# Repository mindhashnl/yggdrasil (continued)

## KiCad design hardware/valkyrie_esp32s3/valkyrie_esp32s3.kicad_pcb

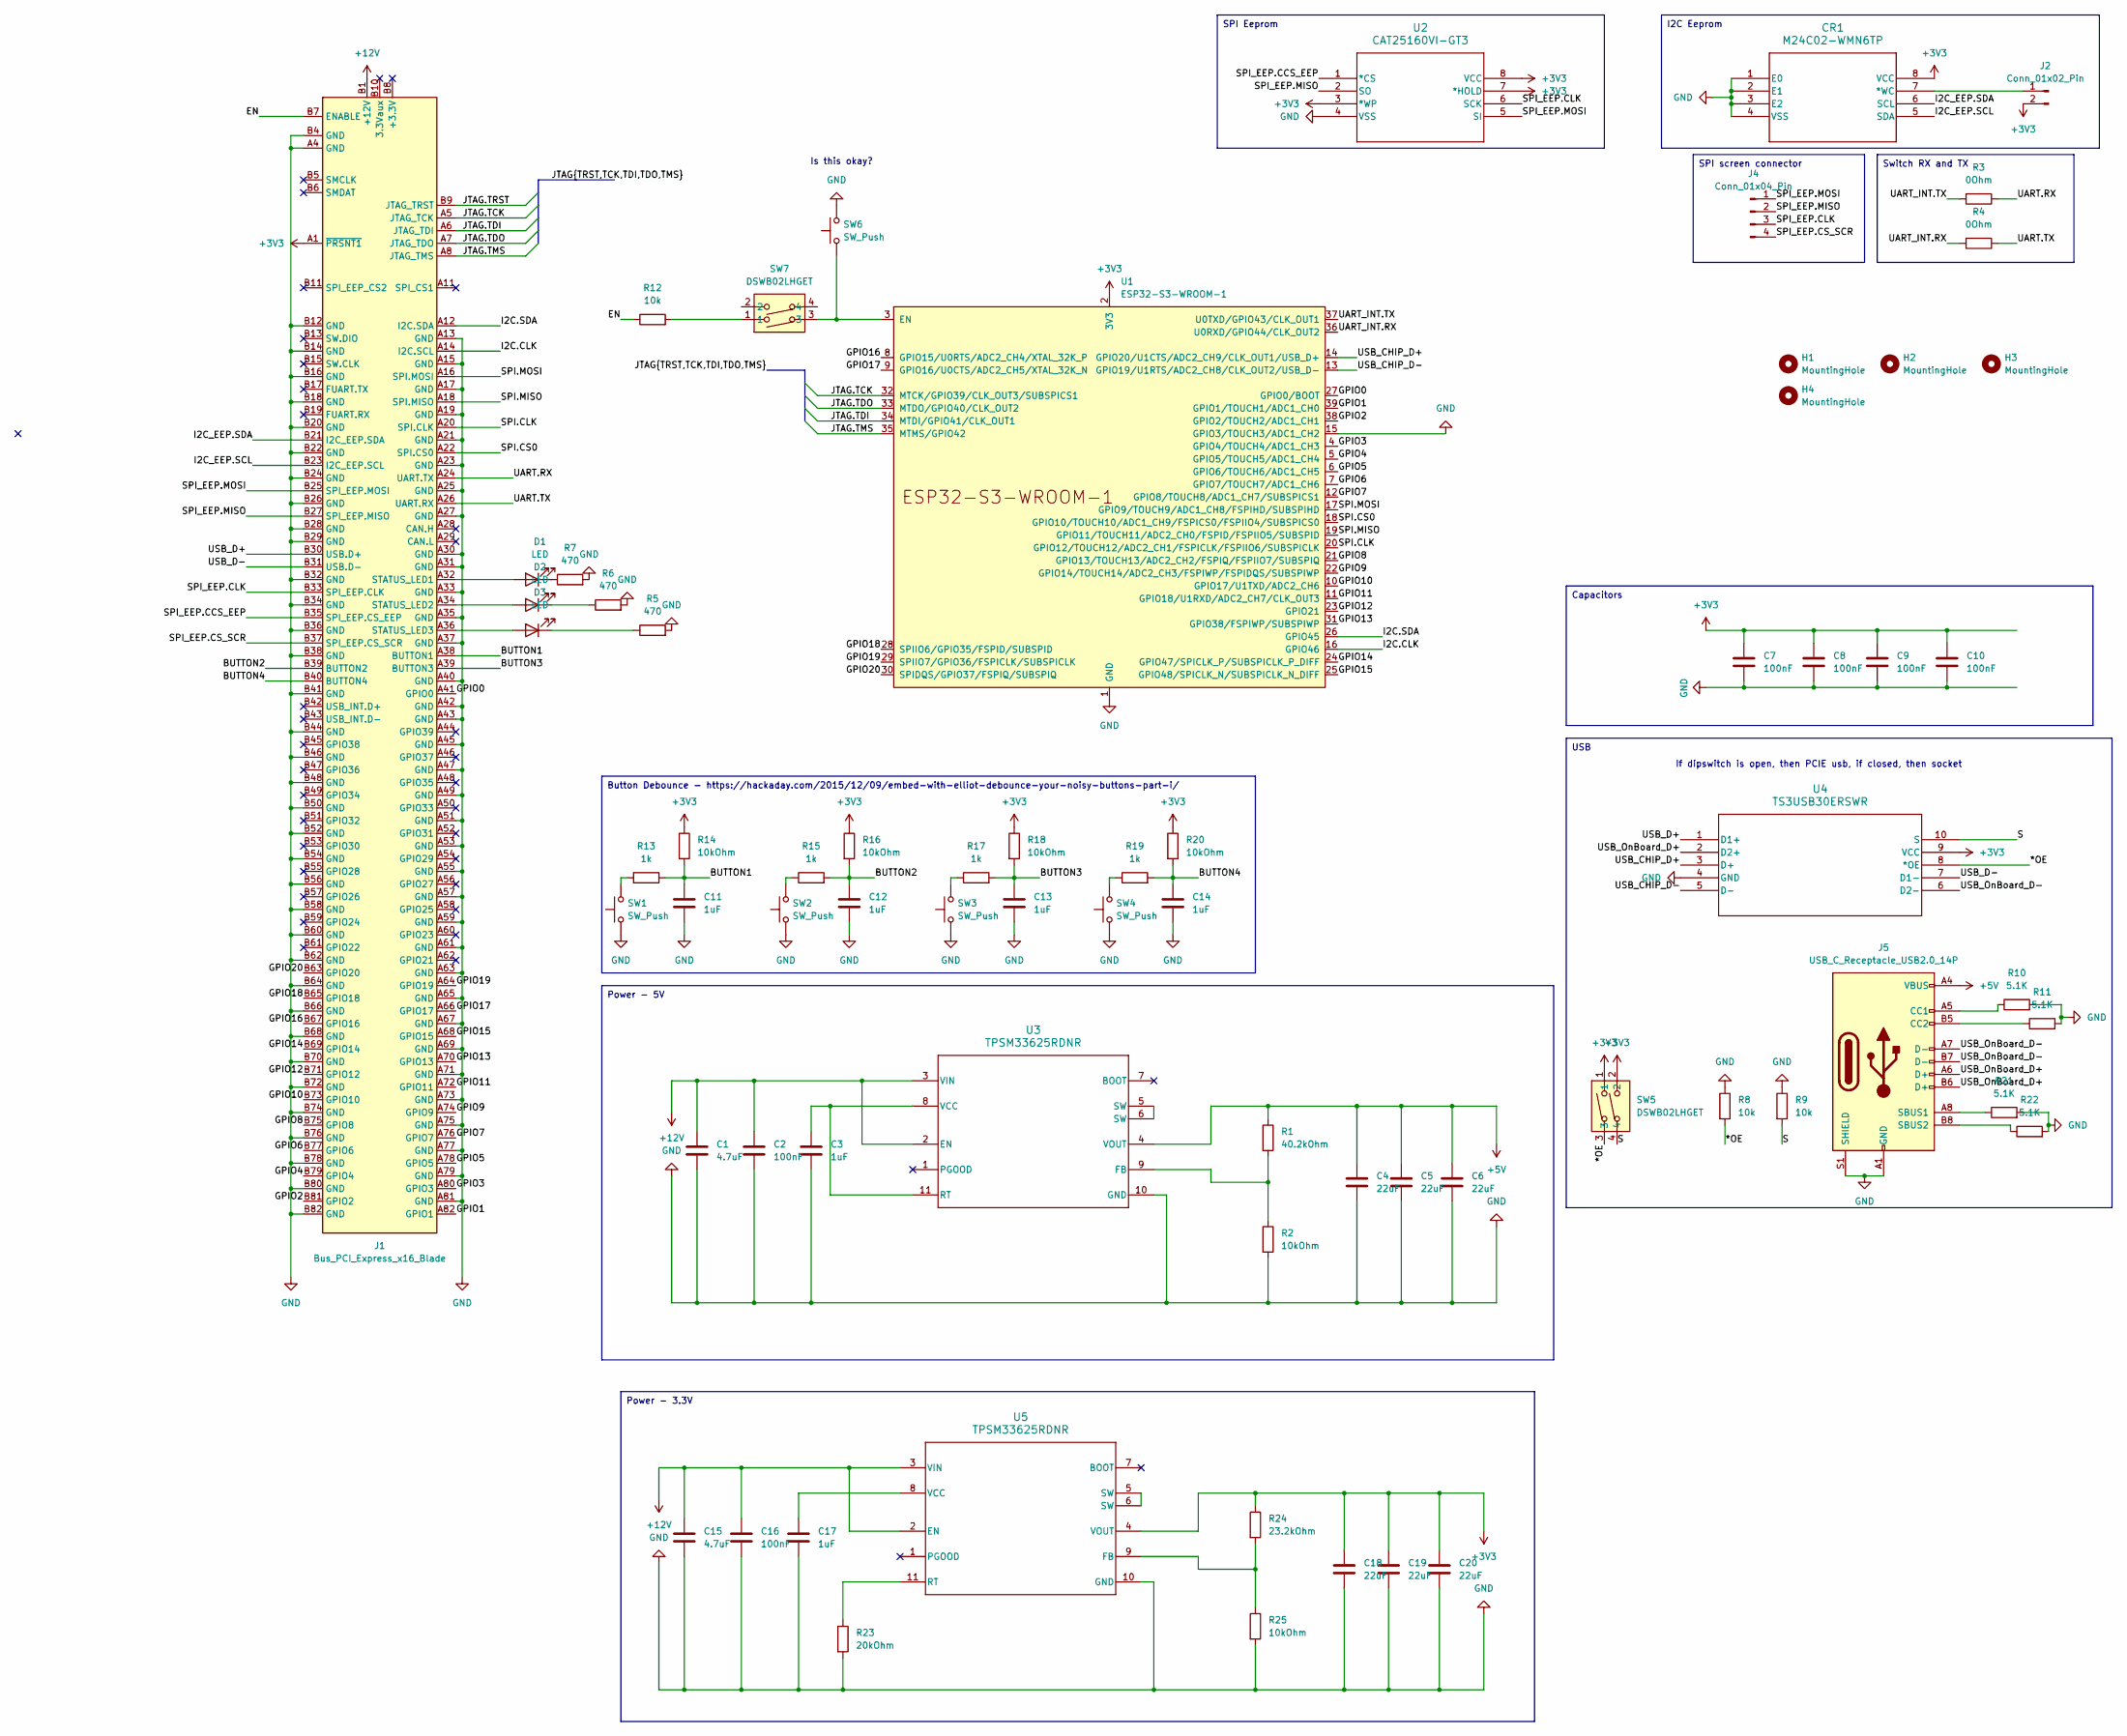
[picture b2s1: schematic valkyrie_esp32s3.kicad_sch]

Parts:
C1, C15: 4.7uF; C_0805_2012Metric
C2, C7, C8, C9, C10, C16: 100nF; C_0805_2012Metric
C3, C11, C12, C13, C14, C17: 1uF; C_0805_2012Metric
C4, C5, C6, C18, C19, C20: 22uF; C_0805_2012Metric
CR1: M24C02-WMN6TP; SO-8_STM
D1, D2, D3: LED; LED_0805_2012Metric
H1, H2, H3, H4: MountingHole; MountingHole_3.2mm_M3_Pad_TopBottom
J1: Bus_PCI_Express_x16_Blade; BUS_PCIexpress_x16
J2: Conn_01x02_Pin; PinHeader_1x02_P2.54mm_Vertical
J4: Conn_01x04_Pin; PinHeader_1x04_P2.54mm_Vertical
J5: USB_C_Receptacle_USB2.0_14P; USB_C_Receptacle_G-Switch_GT-USB-7010ASV
R1: 40.2kOhm; R_0805_2012Metric
R2, R14, R16, R18, R20, R25: 10kOhm; R_0805_2012Metric
R3, R4: 0Ohm; R_0805_2012Metric
R5, R6, R7: 470; R_0805_2012Metric
R8, R9, R12: 10k; R_0805_2012Metric
R10, R11, R21, R22: 5.1K; R_0805_2012Metric
R13, R15, R17, R19: 1k; R_0805_2012Metric
R23: 20kOhm; R_0805_2012Metric
R24: 23.2kOhm; R_0805_2012Metric
SW1, SW2, SW3, SW4, SW6: SW_Push; SW_Push_1P1T_XKB_TS-1187A
SW5, SW7: DSWB02LHGET; SW-TH_DSWB02LHGET; LCSC Part C99421
U1: ESP32-S3-WROOM-1
U2: CAT25160VI-GT3; SOIC8_ONS
U3, U5: TPSM33625RDNR; RDN0011A-MFG_custom
U4: TS3USB30ERSWR; RSW10_TEX

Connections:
+3V3: C7.1, C8.1, C9.1, C10.1, C18.1, C19.1, C20.1, CR1.8 (VCC), J1.A1 (~PRSNT1), J2.2, R14.1, R16.1, R18.1, R20.1, R24.1, SW5.1, SW5.2, U1.2 (3V3), U2.3 (*WP), U2.7 (*HOLD), U2.8 (VCC), U4.9 (VCC), U5.4 (VOUT)
+5V: C4.1, C5.1, C6.1, J5.A4 (VBUS), J5.A9 (VBUS), J5.B4 (VBUS), J5.B9 (VBUS), R1.1, U3.4 (VOUT)
+12V: C1.1, C2.1, C15.1, C16.1, J1.A2 (+12V), J1.A3 (+12V), J1.B1 (+12V), J1.B2 (+12V), J1.B3 (+12V), U3.2 (EN), U3.3 (VIN), U5.2 (EN), U5.3 (VIN)
/*OE: R8.2, SW5.3, U4.8 (*OE)
/BUTTON1: C11.1, J1.A38 (BUTTON1), R13.2, R14.2
/BUTTON2: C12.1, J1.B39 (BUTTON2), R15.2, R16.2
/BUTTON3: C13.1, J1.A39 (BUTTON3), R17.2, R18.2
/BUTTON4: C14.1, J1.B40 (BUTTON4), R19.2, R20.2
/EN: J1.B7 (ENABLE), R12.1
/GPIO0: J1.A41 (GPIO0), U1.27 (GPIO0/BOOT)
/GPIO1: J1.A82 (GPIO1), U1.39 (GPIO1/TOUCH1/ADC1_CH0)
/GPIO2: J1.B81 (GPIO2), U1.38 (GPIO2/TOUCH2/ADC1_CH1)
/GPIO3: J1.A80 (GPIO3), U1.4 (GPIO4/TOUCH4/ADC1_CH3)
/GPIO4: J1.B79 (GPIO4), U1.5 (GPIO5/TOUCH5/ADC1_CH4)
/GPIO5: J1.A78 (GPIO5), U1.6 (GPIO6/TOUCH6/ADC1_CH5)
/GPIO6: J1.B77 (GPIO6), U1.7 (GPIO7/TOUCH7/ADC1_CH6)
/GPIO7: J1.A76 (GPIO7), U1.12 (GPIO8/TOUCH8/ADC1_CH7/SUBSPICS1)
/GPIO8: J1.B75 (GPIO8), U1.21 (GPIO13/TOUCH13/ADC2_CH2/FSPIQ/FSPIIO7/S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)
/GPIO9: J1.A74 (GPIO9), U1.22 (GPIO14/TOUCH14/ADC2_CH3/FSPIWP/FSPIDQS/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)
/GPIO10: J1.B73 (GPIO10), U1.10 (GPIO17/U1TXD/ADC2_CH6)
/GPIO11: J1.A72 (GPIO11), U1.11 (GPIO18/U1RXD/ADC2_CH7/CLK_OUT3)
/GPIO12: J1.B71 (GPIO12), U1.23 (GPIO21)
/GPIO13: J1.A70 (GPIO13), U1.31 (GPIO38/FSPIWP/SUBSPIWP)
/GPIO14: J1.B69 (GPIO14), U1.24 (GPIO47/SPICLK_P/SUBSPICLK_P_DIFF)
/GPIO15: J1.A68 (GPIO15), U1.25 (GPIO48/SPICLK_N/SUBSPICLK_N_DIFF)
/GPIO16: J1.B67 (GPIO16), U1.8 (GPIO15/U0RTS/ADC2_CH4/XTAL_32K_P)
/GPIO17: J1.A66 (GPIO17), U1.9 (GPIO16/U0CTS/ADC2_CH5/XTAL_32K_N)
/GPIO18: J1.B65 (GPIO18), U1.28 (SPIIO6/GPIO35/FSPID/SUBSPID)
/GPIO19: J1.A64 (GPIO19), U1.29 (SPIIO7/GPIO36/FSPICLK/SUBSPICLK)
/GPIO20: J1.B63 (GPIO20), U1.30 (SPIDQS/GPIO37/FSPIQ/SUBSPIQ)
/I2C.CLK: J1.A14 (I2C.SCL), U1.16 (GPIO46)
/I2C.SDA: J1.A12 (I2C.SDA), U1.26 (GPIO45)
/I2C_EEP.SCL: CR1.5 (SDA), J1.B23 (I2C_EEP.SCL)
/I2C_EEP.SDA: CR1.6 (SCL), J1.B21 (I2C_EEP.SDA)
/JTAG.TCK: J1.A5 (JTAG_TCK), U1.32 (MTCK/GPIO39/CLK_OUT3/SUBSPICS1)
/JTAG.TDI: J1.A6 (JTAG_TDI), U1.34 (MTDI/GPIO41/CLK_OUT1)
/JTAG.TDO: J1.A7 (JTAG_TDO), U1.33 (MTDO/GPIO40/CLK_OUT2)
/JTAG.TMS: J1.A8 (JTAG_TMS), U1.35 (MTMS/GPIO42)
/JTAG.TRST: J1.B9 (JTAG_TRST)
/S: R9.2, SW5.4, U4.10 (S)
/SPI.CLK: J1.A20 (SPI.CLK), U1.20 (GPIO12/TOUCH12/ADC2_CH1/FSPICLK/FSPIIO6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)
/SPI.CS0: J1.A22 (SPI.CS0), U1.18 (GPIO10/TOUCH10/ADC1_CH9/FSPICS0/FSPIIO4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)
/SPI.MISO: J1.A18 (SPI.MISO), U1.19 (GPIO11/TOUCH11/ADC2_CH0/FSPID/FSPIIO5/S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)
/SPI.MOSI: J1.A16 (SPI.MOSI), U1.17 (GPIO9/TOUCH9/ADC1_CH8/FSPIHD/SUBSPIHD)
/SPI_EEP.CCS_EEP: J1.B35 (SPI_EEP.CS_EEP), U2.1 (*CS)
/SPI_EEP.CLK: J1.B33 (SPI_EEP.CLK), J4.3, U2.6 (SCK)
/SPI_EEP.CS_SCR: J1.B37 (SPI_EEP.CS_SCR), J4.4
/SPI_EEP.MISO: J1.B27 (SPI_EEP.MISO), J4.2, U2.2 (SO)
/SPI_EEP.MOSI: J1.B25 (SPI_EEP.MOSI), J4.1, U2.5 (SI)
/UART.RX: J1.A24 (UART.TX), R3.1
/UART.TX: J1.A26 (UART.RX), R4.1
/UART_INT.RX: R4.2, U1.36 (U0RXD/GPIO44/CLK_OUT2)
/UART_INT.TX: R3.2, U1.37 (U0TXD/GPIO43/CLK_OUT1)
/USB_CHIP_D+: U1.14 (GPIO20/U1CTS/ADC2_CH9/CLK_OUT1/USB_D+), U4.3 (D+)
/USB_CHIP_D-: U1.13 (GPIO19/U1RTS/ADC2_CH8/CLK_OUT2/USB_D-), U4.5 (D-)
/USB_D+: J1.B30 (USB.D+), U4.1 (D1+)
/USB_D-: J1.B31 (USB.D-), U4.7 (D1-)
/USB_OnBoard_D+: J5.A6 (D+), J5.B6 (D+), U4.2 (D2+)
/USB_OnBoard_D-: J5.A7 (D-), J5.B7 (D-), U4.6 (D2-)
GND: C1.2, C2.2, C3.2, C4.2, C5.2, C6.2, C7.2, C8.2, C9.2, C10.2, C11.2, C12.2, C13.2, C14.2, C15.2, C16.2, C17.2, C18.2, C19.2, C20.2, CR1.1 (E0), CR1.2 (E1), CR1.3 (E2), CR1.4 (VSS), J1.A4 (GND), J1.A13 (GND), J1.A15 (GND), J1.A17 (GND), J1.A19 (GND), J1.A21 (GND), J1.A23 (GND), J1.A25 (GND), J1.A27 (GND), J1.A30 (GND), J1.A31 (GND), J1.A33 (GND), J1.A35 (GND), J1.A37 (GND), J1.A40 (GND), J1.A42 (GND), J1.A43 (GND), J1.A45 (GND), J1.A47 (GND), J1.A49 (GND), J1.A51 (GND), J1.A53 (GND), J1.A55 (GND), J1.A57 (GND), J1.A59 (GND), J1.A61 (GND), J1.A63 (GND), J1.A65 (GND), J1.A67 (GND), J1.A69 (GND), J1.A71 (GND), J1.A73 (GND), J1.A75 (GND), J1.A77 (GND), J1.A79 (GND), J1.A81 (GND), J1.B4 (GND), J1.B12 (GND), J1.B14 (GND), J1.B16 (GND), J1.B18 (GND), J1.B20 (GND), J1.B22 (GND), J1.B24 (GND), J1.B26 (GND), J1.B28 (GND), J1.B29 (GND), J1.B32 (GND), J1.B34 (GND), J1.B36 (GND), J1.B38 (GND), J1.B41 (GND), J1.B44 (GND), J1.B46 (GND), J1.B48 (GND), J1.B50 (GND), J1.B52 (GND), J1.B54 (GND), J1.B56 (GND), J1.B58 (GND), J1.B60 (GND), J1.B62 (GND), J1.B64 (GND), J1.B66 (GND), J1.B68 (GND), J1.B70 (GND), J1.B72 (GND), J1.B74 (GND), J1.B76 (GND), J1.B78 (GND), J1.B80 (GND), J1.B82 (GND), J5.A1 (GND), J5.A12 (GND), J5.B1 (GND), J5.B12 (GND), J5.S1 (SHIELD), R2.2, R5.2, R6.2, R7.2, R8.1, R9.1, R10.2, R11.2, R21.2, R22.2, R23.2, R25.2, SW1.1, SW2.1, SW3.1, SW4.1, SW6.2, U1.1 (GND), U1.15 (GPIO3/TOUCH3/ADC1_CH2), U1.40 (GND), U1.41 (GND), U2.4 (VSS), U3.10 (GND), U4.4 (GND), U5.10 (GND)
unnamed: CR1.7 (*WC), J2.1
unnamed: D1.2 (A), J1.A32 (STATUS_LED1)
unnamed: D1.1 (K), R7.1
unnamed: D2.2 (A), J1.A34 (STATUS_LED2)
unnamed: D2.1 (K), R6.1
unnamed: D3.2 (A), J1.A36 (STATUS_LED3)
unnamed: D3.1 (K), R5.1
unnamed: J5.A5 (CC1), R10.1
unnamed: J5.B5 (CC2), R11.1
unnamed: J5.A8 (SBUS1), R21.1
unnamed: J5.B8 (SBUS2), R22.1
unnamed: R12.2, SW7.1
unnamed: R13.1, SW1.2
unnamed: R15.1, SW2.2
unnamed: R17.1, SW3.2
unnamed: R19.1, SW4.2
unnamed: SW6.1, SW7.3, U1.3 (EN)
unnamed: R1.2, R2.1, U3.9 (FB)
unnamed: C3.1, U3.8 (VCC), U3.11 (RT)
unnamed: U3.5 (SW), U3.6 (SW)
unnamed: R24.2, R25.1, U5.9 (FB)
unnamed: R23.1, U5.11 (RT)
unnamed: U5.5 (SW), U5.6 (SW)
unnamed: C17.1, U5.8 (VCC)

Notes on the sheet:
Switch RX and TX
Power - 5V
USB
I2C Eeprom
SPI screen connector
SPI Eeprom
Capacitors
Button Debounce - https://hackaday.com/2015/12/09/embed-with-elliot-debounce-your-noisy-buttons-part-i/
Power - 3.3V
Is this okay?
If dipswitch is open, then PCIE usb, if closed, then socket

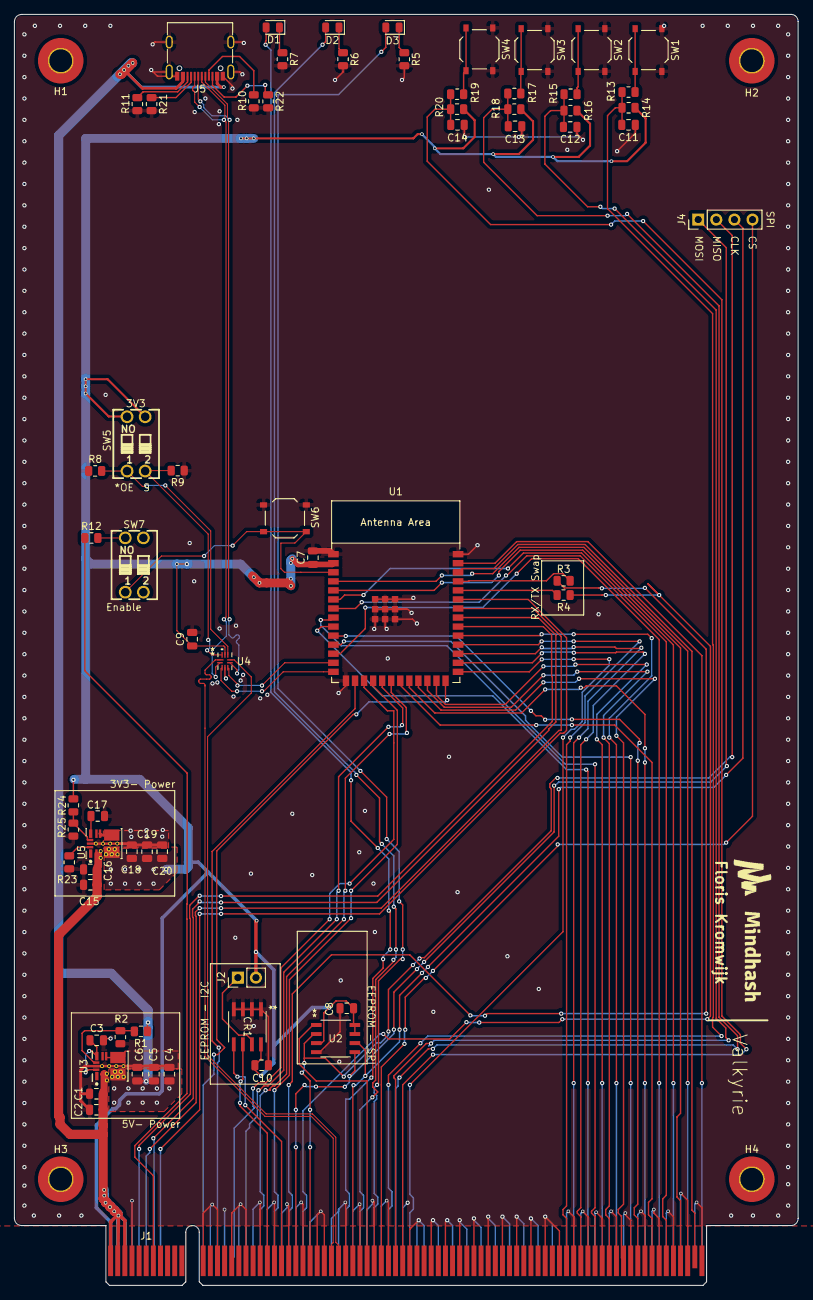
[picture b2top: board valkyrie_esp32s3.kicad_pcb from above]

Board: 4 copper layers, 110.0 x 178.4 mm, 69 parts (0 on the bottom side), 83 nets.

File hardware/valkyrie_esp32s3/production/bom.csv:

Designator,Footprint,Quantity,Value,LCSC Part #
"C1, C15",0805,2,4.7uF,
"C10, C16, C2, C7, C8, C9",0805,6,100nF,
"C11, C12, C13, C14, C17, C3",0805,6,1uF,
"C18, C19, C20, C4, C5, C6",0805,6,22uF,
CR1,SO-8_STM,1,M24C02-WMN6TP,
"D1, D2, D3",0805,3,LED,
J1,BUS_PCIexpress_x16,1,Bus_PCI_Express_x16_Blade,
J2,PinHeader_1x02_P2.54mm_Vertical,1,Conn_01x02_Pin,
J4,PinHeader_1x04_P2.54mm_Vertical,1,Conn_01x04_Pin,
J5,USB_C_Receptacle_G-Switch_GT-USB-7010ASV,1,USB_C_Receptacle_USB2.0_14P,
R1,0805,1,40.2kOhm,
"R10, R11, R21, R22",0805,4,5.1K,
"R12, R8, R9",0805,3,10k,
"R13, R15, R17, R19",0805,4,1k,
"R14, R16, R18, R2, R20, R25",0805,6,10kOhm,
R23,0805,1,20kOhm,
R24,0805,1,23.2kOhm,
"R3, R4",0805,2,0Ohm,
"R5, R6, R7",0805,3,470,
"SW1, SW2, SW3, SW4, SW6",SW_Push_1P1T_XKB_TS-1187A,5,SW_Push,
"SW5, SW7",SW-TH_DSWB02LHGET,2,DSWB02LHGET,
U1,ESP32-S3-WROOM-1,1,ESP32-S3-WROOM-1,
U2,SOIC8_ONS,1,CAT25160VI-GT3,
"U3, U5",RDN0011A-MFG_custom,2,TPSM33625RDNR,
U4,RSW10_TEX,1,TS3USB30ERSWR,

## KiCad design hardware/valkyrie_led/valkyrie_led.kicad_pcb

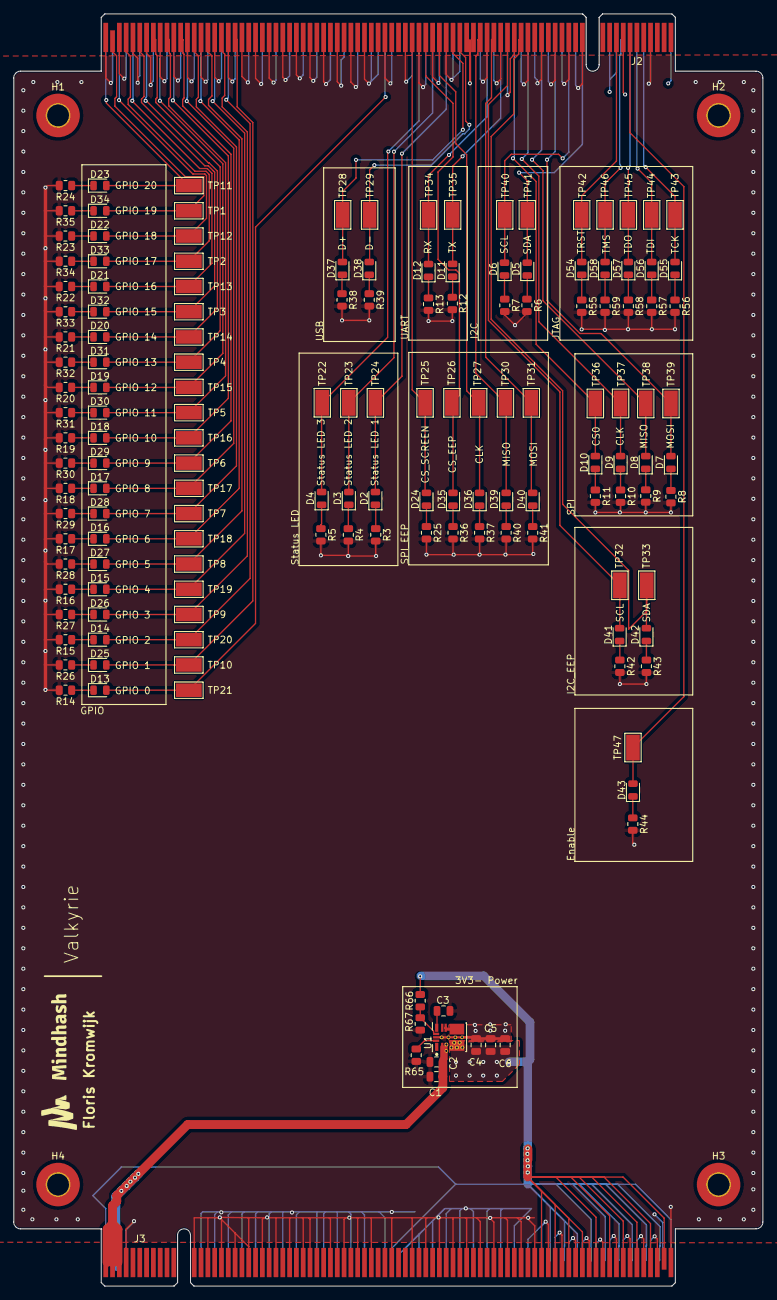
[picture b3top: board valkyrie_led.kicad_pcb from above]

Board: 4 copper layers, 110.0 x 186.8 mm, 157 parts (0 on the bottom side), 102 nets.

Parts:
C1: 4.7uF; C_0805_2012Metric
C2: 100nF; C_0805_2012Metric
C3: 1uF; C_0805_2012Metric
C4, C5, C6: 22uF; C_0805_2012Metric
D2, D3, D4, D5, D6, D7, D8, D9, D10, D11, D12, D13, D14, D15, D16, D17, D18, D19, D20, D21, D22, D23, D24, D25, D26, D27, D28, D29, D30, D31, D32, D33, D34, D35, D36, D37, D38, D39, D40, D41, D42, D43, D54, D55, D56, D57, D58: LED; LED_0805_2012Metric
H1, H2, H3, H4: MountingHole; MountingHole_3.2mm_M3_Pad_TopBottom
J2, J3: Bus_PCI_Express_x16_Blade; BUS_PCIexpress_x16
R3, R4, R5, R6, R7, R8, R9, R10, R11, R12, R13, R14, R15, R16, R17, R18, R19, R20, R21, R22, R23, R24, R25, R26, R27, R28, R29, R30, R31, R32, R33, R34, R35, R36, R37, R38, R39, R40, R41, R42, R43, R44, R55, R56, R57, R58, R59: 470; R_0805_2012Metric
R65: 20kOhm; R_0805_2012Metric
R66: 23.2kOhm; R_0805_2012Metric
R67: 10kOhm; R_0805_2012Metric
TP1, TP2, TP3, TP4, TP5, TP6, TP7, TP8, TP9, TP10, TP11, TP12, TP13, TP14, TP15, TP16, TP17, TP18, TP19, TP20, TP21, TP22, TP23, TP24, TP25, TP26, TP27, TP28, TP29, TP30, TP31, TP32, TP33, TP34, TP35, TP36, TP37, TP38, TP39, TP40, TP41, TP42, TP43, TP44, TP45, TP46, TP47: TestPoint; TestPoint_Keystone_5019_Minature
U1: TPSM33625RDNR; RDN0011A-MFG_custom

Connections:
+3.3V: J2.A1 (~PRSNT1), J2.A9 (+3.3V), J2.A10 (+3.3V), J2.B8 (+3.3V)
+3V3: C4.1, C5.1, C6.1, J3.A1 (~PRSNT1), J3.A41 (GPIO0), J3.A64 (GPIO19), J3.A66 (GPIO17), J3.A68 (GPIO15), J3.A70 (GPIO13), J3.A72 (GPIO11), J3.A74 (GPIO9), J3.A76 (GPIO7), J3.A78 (GPIO5), J3.A80 (GPIO3), J3.A82 (GPIO1), J3.B63 (GPIO20), J3.B65 (GPIO18), J3.B67 (GPIO16), J3.B69 (GPIO14), J3.B71 (GPIO12), J3.B73 (GPIO10), J3.B75 (GPIO8), J3.B77 (GPIO6), J3.B79 (GPIO4), J3.B81 (GPIO2), R66.1, U1.4 (VOUT)
+12V: C1.1, C2.1, J3.A2 (+12V), J3.A3 (+12V), J3.B1 (+12V), J3.B2 (+12V), J3.B3 (+12V), U1.2 (EN), U1.3 (VIN)
GND: C1.2, C2.2, C3.2, C4.2, C5.2, C6.2, J2.A4 (GND), J2.A13 (GND), J2.A15 (GND), J2.A17 (GND), J2.A19 (GND), J2.A21 (GND), J2.A23 (GND), J2.A25 (GND), J2.A27 (GND), J2.A30 (GND), J2.A31 (GND), J2.A33 (GND), J2.A35 (GND), J2.A37 (GND), J2.A40 (GND), J2.A42 (GND), J2.A43 (GND), J2.A45 (GND), J2.A47 (GND), J2.A49 (GND), J2.A51 (GND), J2.A53 (GND), J2.A55 (GND), J2.A57 (GND), J2.A59 (GND), J2.A61 (GND), J2.A63 (GND), J2.A65 (GND), J2.A67 (GND), J2.A69 (GND), J2.A71 (GND), J2.A73 (GND), J2.A75 (GND), J2.A77 (GND), J2.A79 (GND), J2.A81 (GND), J2.B4 (GND), J2.B12 (GND), J2.B14 (GND), J2.B16 (GND), J2.B18 (GND), J2.B20 (GND), J2.B22 (GND), J2.B24 (GND), J2.B26 (GND), J2.B28 (GND), J2.B29 (GND), J2.B32 (GND), J2.B34 (GND), J2.B36 (GND), J2.B38 (GND), J2.B41 (GND), J2.B44 (GND), J2.B46 (GND), J2.B48 (GND), J2.B50 (GND), J2.B52 (GND), J2.B54 (GND), J2.B56 (GND), J2.B58 (GND), J2.B60 (GND), J2.B62 (GND), J2.B64 (GND), J2.B66 (GND), J2.B68 (GND), J2.B70 (GND), J2.B72 (GND), J2.B74 (GND), J2.B76 (GND), J2.B78 (GND), J2.B80 (GND), J2.B82 (GND), J3.A4 (GND), J3.A13 (GND), J3.A15 (GND), J3.A17 (GND), J3.A19 (GND), J3.A21 (GND), J3.A23 (GND), J3.A25 (GND), J3.A27 (GND), J3.A30 (GND), J3.A31 (GND), J3.A33 (GND), J3.A35 (GND), J3.A37 (GND), J3.A40 (GND), J3.A42 (GND), J3.A43 (GND), J3.A45 (GND), J3.A47 (GND), J3.A49 (GND), J3.A51 (GND), J3.A53 (GND), J3.A55 (GND), J3.A57 (GND), J3.A59 (GND), J3.A61 (GND), J3.A63 (GND), J3.A65 (GND), J3.A67 (GND), J3.A69 (GND), J3.A71 (GND), J3.A73 (GND), J3.A75 (GND), J3.A77 (GND), J3.A79 (GND), J3.A81 (GND), J3.B4 (GND), J3.B12 (GND), J3.B14 (GND), J3.B16 (GND), J3.B18 (GND), J3.B20 (GND), J3.B22 (GND), J3.B24 (GND), J3.B26 (GND), J3.B28 (GND), J3.B29 (GND), J3.B32 (GND), J3.B34 (GND), J3.B36 (GND), J3.B38 (GND), J3.B41 (GND), J3.B44 (GND), J3.B46 (GND), J3.B48 (GND), J3.B50 (GND), J3.B52 (GND), J3.B54 (GND), J3.B56 (GND), J3.B58 (GND), J3.B60 (GND), J3.B62 (GND), J3.B64 (GND), J3.B66 (GND), J3.B68 (GND), J3.B70 (GND), J3.B72 (GND), J3.B74 (GND), J3.B76 (GND), J3.B78 (GND), J3.B80 (GND), J3.B82 (GND), R3.2, R4.2, R5.2, R6.2, R7.2, R8.2, R9.2, R10.2, R11.2, R12.2, R13.2, R14.2, R15.2, R16.2, R17.2, R18.2, R19.2, R20.2, R21.2, R22.2, R23.2, R24.2, R25.2, R26.2, R27.2, R28.2, R29.2, R30.2, R31.2, R32.2, R33.2, R34.2, R35.2, R36.2, R37.2, R38.2, R39.2, R40.2, R41.2, R42.2, R43.2, R44.2, R55.2, R56.2, R57.2, R58.2, R59.2, R65.2, R67.2, U1.10 (GND)
unnamed: D2.2 (A), J2.A32 (STATUS_LED1), TP24.1
unnamed: D2.1 (K), R3.1
unnamed: D3.2 (A), J2.A34 (STATUS_LED2), TP23.1
unnamed: D3.1 (K), R4.1
unnamed: D4.2 (A), J2.A36 (STATUS_LED3), TP22.1
unnamed: D4.1 (K), R5.1
unnamed: D5.2 (A), J2.A12 (I2C.SDA), TP41.1
unnamed: D5.1 (K), R6.1
unnamed: D6.2 (A), J2.A14 (I2C.SCL), TP40.1
unnamed: D6.1 (K), R7.1
unnamed: D7.2 (A), J2.A16 (SPI.MOSI), TP39.1
unnamed: D7.1 (K), R8.1
unnamed: D8.2 (A), J2.A18 (SPI.MISO), TP38.1
unnamed: D8.1 (K), R9.1
unnamed: D9.2 (A), J2.A20 (SPI.CLK), TP37.1
unnamed: D9.1 (K), R10.1
unnamed: D10.2 (A), J2.A22 (SPI.CS0), TP36.1
unnamed: D10.1 (K), R11.1
unnamed: D11.2 (A), J2.A24 (UART.TX), TP35.1
unnamed: D11.1 (K), R12.1
unnamed: D12.2 (A), J2.A26 (UART.RX), TP34.1
unnamed: D12.1 (K), R13.1
unnamed: D13.2 (A), J2.A41 (GPIO0), TP21.1
unnamed: D13.1 (K), R14.1
unnamed: D14.2 (A), J2.A64 (GPIO19), TP20.1
unnamed: D14.1 (K), R15.1
unnamed: D15.2 (A), J2.A66 (GPIO17), TP19.1
unnamed: D15.1 (K), R16.1
unnamed: D16.2 (A), J2.A68 (GPIO15), TP18.1
unnamed: D16.1 (K), R17.1
unnamed: D17.2 (A), J2.A70 (GPIO13), TP17.1
unnamed: D17.1 (K), R18.1
unnamed: D18.2 (A), J2.A72 (GPIO11), TP16.1
unnamed: D18.1 (K), R19.1
unnamed: D19.2 (A), J2.A74 (GPIO9), TP15.1
unnamed: D19.1 (K), R20.1
unnamed: D20.2 (A), J2.A76 (GPIO7), TP14.1
unnamed: D20.1 (K), R21.1
unnamed: D21.2 (A), J2.A78 (GPIO5), TP13.1
unnamed: D21.1 (K), R22.1
unnamed: D22.2 (A), J2.A80 (GPIO3), TP12.1
unnamed: D22.1 (K), R23.1
unnamed: D23.2 (A), J2.A82 (GPIO1), TP11.1
unnamed: D23.1 (K), R24.1
unnamed: D24.2 (A), J2.B37 (SPI_EEP.CS_SCR), TP25.1
unnamed: D24.1 (K), R25.1
unnamed: D25.2 (A), J2.B63 (GPIO20), TP10.1
unnamed: D25.1 (K), R26.1
unnamed: D26.2 (A), J2.B65 (GPIO18), TP9.1
unnamed: D26.1 (K), R27.1
unnamed: D27.2 (A), J2.B67 (GPIO16), TP8.1
unnamed: D27.1 (K), R28.1
unnamed: D28.2 (A), J2.B69 (GPIO14), TP7.1
unnamed: D28.1 (K), R29.1
unnamed: D29.2 (A), J2.B71 (GPIO12), TP6.1
unnamed: D29.1 (K), R30.1
unnamed: D30.2 (A), J2.B73 (GPIO10), TP5.1
unnamed: D30.1 (K), R31.1
unnamed: D31.2 (A), J2.B75 (GPIO8), TP4.1
unnamed: D31.1 (K), R32.1
unnamed: D32.2 (A), J2.B77 (GPIO6), TP3.1
unnamed: D32.1 (K), R33.1
unnamed: D33.2 (A), J2.B79 (GPIO4), TP2.1
unnamed: D33.1 (K), R34.1
unnamed: D34.2 (A), J2.B81 (GPIO2), TP1.1
unnamed: D34.1 (K), R35.1
unnamed: D35.2 (A), J2.B35 (SPI_EEP.CS_EEP), TP26.1
unnamed: D35.1 (K), R36.1
unnamed: D36.2 (A), J2.B33 (SPI_EEP.CLK), TP27.1
unnamed: D36.1 (K), R37.1
unnamed: D37.2 (A), J2.B31 (USB.D-), TP28.1
unnamed: D37.1 (K), R38.1
unnamed: D38.2 (A), J2.B30 (USB.D+), TP29.1
unnamed: D38.1 (K), R39.1
unnamed: D39.2 (A), J2.B27 (SPI_EEP.MISO), TP30.1
unnamed: D39.1 (K), R40.1
unnamed: D40.2 (A), J2.B25 (SPI_EEP.MOSI), TP31.1
unnamed: D40.1 (K), R41.1
unnamed: D41.2 (A), J2.B23 (I2C_EEP.SCL), TP32.1
unnamed: D41.1 (K), R42.1
unnamed: D42.2 (A), J2.B21 (I2C_EEP.SDA), TP33.1
unnamed: D42.1 (K), R43.1
unnamed: D43.2 (A), J2.B7 (ENABLE), TP47.1
unnamed: D43.1 (K), R44.1
unnamed: D54.2 (A), J2.B9 (JTAG_TRST), TP42.1
unnamed: D54.1 (K), R55.1
unnamed: D55.2 (A), J2.A5 (JTAG_TCK), TP43.1
unnamed: D55.1 (K), R56.1
unnamed: D56.2 (A), J2.A6 (JTAG_TDI), TP44.1
unnamed: D56.1 (K), R57.1
unnamed: D57.2 (A), J2.A7 (JTAG_TDO), TP45.1
unnamed: D57.1 (K), R58.1
unnamed: D58.2 (A), J2.A8 (JTAG_TMS), TP46.1
unnamed: D58.1 (K), R59.1
unnamed: R66.2, R67.1, U1.9 (FB)
unnamed: R65.1, U1.11 (RT)
unnamed: U1.5 (SW), U1.6 (SW)
unnamed: C3.1, U1.8 (VCC)

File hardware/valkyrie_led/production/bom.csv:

Designator,Footprint,Quantity,Value,LCSC Part #
C1,0805,1,4.7uF,
C2,0805,1,100nF,
C3,0805,1,1uF,
"C4, C5, C6",0805,3,22uF,
"D10, D11, D12, D13, D14, D15, D16, D17, D18, D19, D2, D20, D21, D22, D23, D24, D25, D26, D27, D28, D29, D3, D30, D31, D32, D33, D34, D35, D36, D37, D38, D39, D4, D40, D41, D42, D43, D5, D54, D55, D56, D57, D58, D6, D7, D8, D9",0805,47,LED,
"J2, J3",BUS_PCIexpress_x16,2,Bus_PCI_Express_x16_Blade,
"R10, R11, R12, R13, R14, R15, R16, R17, R18, R19, R20, R21, R22, R23, R24, R25, R26, R27, R28, R29, R3, R30, R31, R32, R33, R34, R35, R36, R37, R38, R39, R4, R40, R41, R42, R43, R44, R5, R55, R56, R57, R58, R59, R6, R7, R8, R9",0805,47,470,
R65,0805,1,20kOhm,
R66,0805,1,23.2kOhm,
R67,0805,1,10kOhm,
"TP1, TP10, TP11, TP12, TP13, TP14, TP15, TP16, TP17, TP18, TP19, TP2, TP20, TP21, TP22, TP23, TP24, TP25, TP26, TP27, TP28, TP29, TP3, TP30, TP31, TP32, TP33, TP34, TP35, TP36, TP37, TP38, TP39, TP4, TP40, TP41, TP42, TP43, TP44, TP45, TP46, TP47, TP5, TP6, TP7, TP8, TP9",TestPoint_Keystone_5019_Minature,47,TestPoint,
U1,RDN0011A-MFG_custom,1,TPSM33625RDNR,

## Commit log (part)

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2026-06-13 Initial commit Hardware V2
